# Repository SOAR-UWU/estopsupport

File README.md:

# Emergency-Stop Support Circuit
Driver Circuit for a Kilovac EV200 Contactor.
Takes two switch inputs which are expected to run at 5V with low current.

Theoretically, this can accept any relay or contactor that:
- has sufficiently high coil voltage, matched to the battery input, or uses a coil economiser
- has in-built back-emf suppression

# Variant: Integrated Automotive Relay
See relay branch for details - board designed to consolidate parts for the sake of compactness.

# Expected Operating Range

| Name            | Value     | Unit |
| --------------- | --------- | ---- |
| Battery Voltage | 12 - 16.8 | V    |
| Battery Current | ≤ 3       | A    |
| Signal Voltage  | 5         | V    |
| Signal Current  | 0 - 1     | A    |
| Tap Voltage     | 3.3       | V    |
| Tap Current     | 1.5       | A    |
| Sense Resistor Voltage | 0.33 | V |
| Sense Resistor Voltage (Fault) | 5.2 | V |

# [BTS6163D PROFET](https://www.infineon.com/assets/row/public/documents/10/49/infineon-bts6163d-ds-en.pdf?fileId=5546d4625a888733015aa3da01a1101e)
This circuit is primarily based on the BTS6163 PROFET, which behaves like a P-type MOSFET.
It is chosen due to the fault protection capabilities - it will fail open.

## Sense Resistor
There is a 1 kOhm resistor on the right side of the board that indicates whether the BTS6163D PROFET is in a fault condition.
Fault conditions generally include: Short circuit, overtemperature, overload.

# Opto-isolation
The 5V Signal side (left) is opto-isolated from the Battery Voltage side (right).
Opto-coupler was chosen over a MOSFET such that the 5V side can control the higher voltage side without a risk of shorting battery voltage (16.8V) to the 5V rail.

# Split ground planes
If separate power sources are used for 5V and Battery, both sides will be totally decoupled.
This reduces electromagnetic interference - but is not important in this circuit, as it does not work with sensitive signals.

# Order Parameters
Material: FR-4
Layers: 2
Copper Weight: 1 oz

# Recommended Wiring

Normal Operation

5V Relay Control

Battery voltage side is not used. This is because the PROFET has a threshold voltage of 5.5V.

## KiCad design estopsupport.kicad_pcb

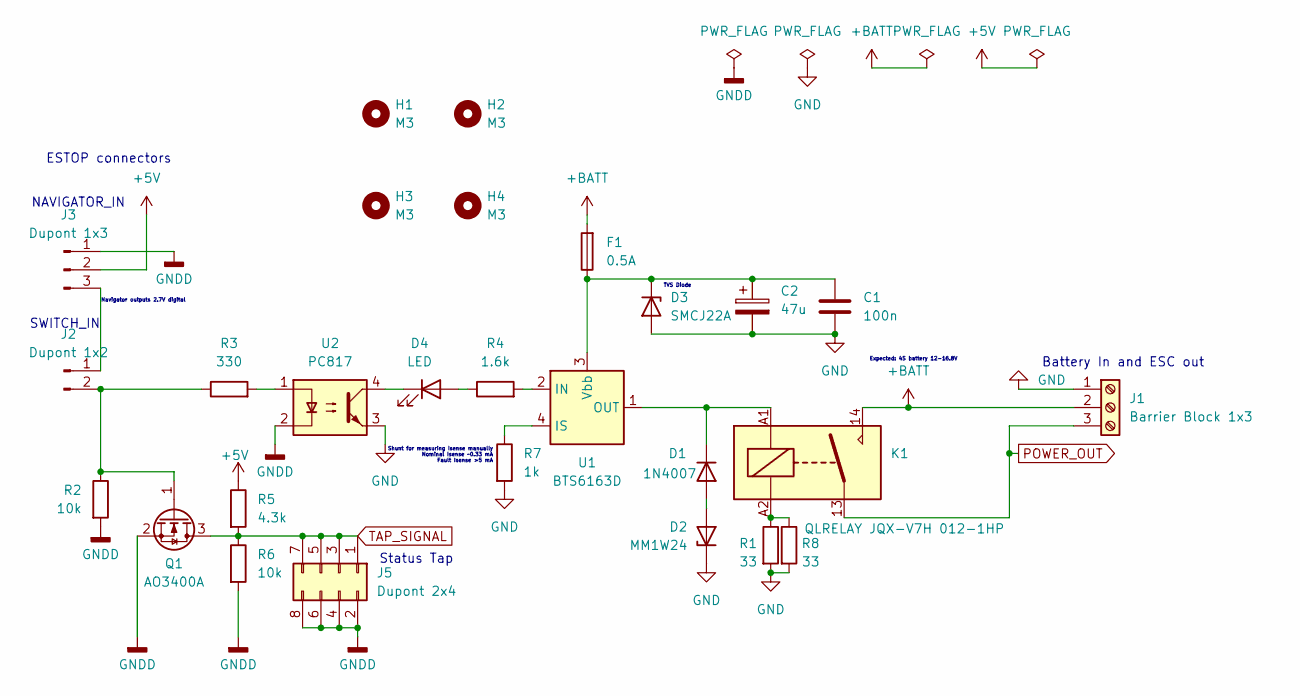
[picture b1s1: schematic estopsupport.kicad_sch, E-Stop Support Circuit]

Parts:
C1: 100n; C_1206_3216Metric; JLCPCB Part # C24497
C2: 47u; CP_Elec_6.3x5.4; JLCPCB Part # C48543040
D1: 1N4007; D_SMA
D2: MM1W24; D_SOD-123
D3: SMCJ22A; D_SMC
D4: LED; LED_D3.0mm
F1: 0.5A; Fuse_1206_3216Metric_Pad1.42x1.75mm_HandSolder
H1, H2, H3, H4: M3; MountingHole_3.2mm_M3
J1: Barrier Block 1x3; CONN-TH_KF88SA-16.0-3P
J2: Dupont 1x2; PinHeader_1x02_P2.54mm_Horizontal
J3: Dupont 1x3; PinHeader_1x03_P2.54mm_Horizontal
J5: Dupont 2x4; PinSocket_2x04_P2.54mm_Vertical
K1: QLRELAY JQX-V7H 012-1HP; RELAY-TH_JQX-V7H-012-1HP
Q1: AO3400A; SOT-23
R1, R8: 33; R_1812_4532Metric
R2, R6: 10k; R_0603_1608Metric
R3: 330; R_0603_1608Metric
R4: 1.6k; R_0603_1608Metric
R5: 4.3k; R_0603_1608Metric
R7: 1k; R_Axial_DIN0204_L3.6mm_D1.6mm_P7.62mm_Horizontal
U1: BTS6163D; TO-252-4; JLCPCB Part # C534821
U2: PC817; DIP-4_W7.62mm; JLCPCB Part # C5350

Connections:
+5V: J3.2, R5.1
+BATT: F1.2, J1.2, K1.14
GND: C1.2, C2.2, D2.1 (K), D3.2 (A), J1.1, R1.2, R7.2, R8.2, U2.3
GNDD: J3.1, J5.2, J5.4, J5.6, J5.8, Q1.2 (S), R2.2, R6.2, U2.2
unnamed: D1.2 (A), D2.2 (A)
unnamed: D1.1 (K), K1.A1, U1.1 (OUT), U1.5 (OUT)
unnamed: C1.1, C2.1, D3.1 (K), F1.1, U1.3 (Vbb)
unnamed: D4.2 (A), R4.1
unnamed: D4.1 (K), U2.4
unnamed: J2.1, J3.3
unnamed: J2.2, Q1.1 (G), R2.1, R3.1
unnamed: K1.A2, R1.1, R8.1
unnamed: R3.2, U2.1
unnamed: R4.2, U1.2 (IN)
unnamed: R7.1, U1.4 (IS)
POWER_OUT: J1.3, K1.13
TAP_SIGNAL: J5.1, J5.3, J5.5, J5.7, Q1.3 (D), R5.2, R6.1

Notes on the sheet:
Status Tap
ESTOP connectors
Shunt for measuring Isense manually Nominal Isense ~0.33 mA Fault Isense >5 mA
Battery In and ESC out
Navigator outputs 2.7V digital
SWITCH_IN
Expected: 4S battery 12-16.8V
TVS Diode
NAVIGATOR_IN

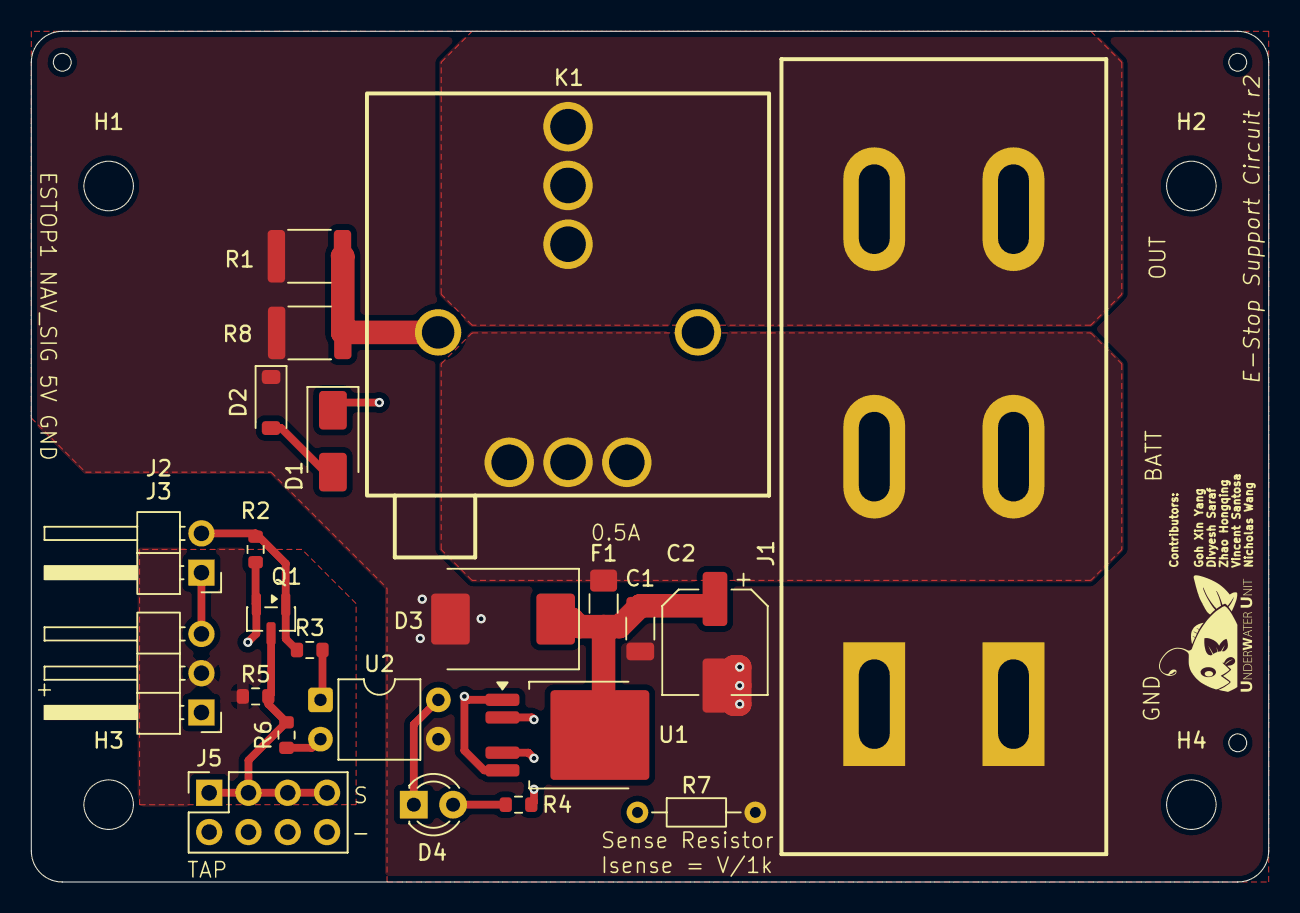
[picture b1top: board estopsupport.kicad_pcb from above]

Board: 4 copper layers, 80.0 x 55.0 mm, 27 parts (0 on the bottom side), 17 nets.

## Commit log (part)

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2026-06-16 initial commit: only low side controlled and unsafe
2026-06-16 feat: add high side relay and suggestions from gemini
2026-06-23 feat: use a profet instead - simpler and more resistant to vibration. TBD: Connector footprint
2026-06-23 chore: add MIT license
2026-06-24 chore: finally settle on Phoenix Contact screw terminal
2026-06-24 refactor: don't rely on adapter board - just design for it to be manually serviced and checked via shunt resistor
2026-06-25 feat: routed pcb
2026-06-26 refactor: use a tht resistor for the shunt - easier to probe and replace
2026-06-26 fix: silkscreen overlap
